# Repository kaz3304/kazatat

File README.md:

# free10u---choc

This fits within the bounds of most cheap or free sample run PCBs. 4x10 ortho with choc spacing and two bottom row options bringing you a total of 32 to 36 keys

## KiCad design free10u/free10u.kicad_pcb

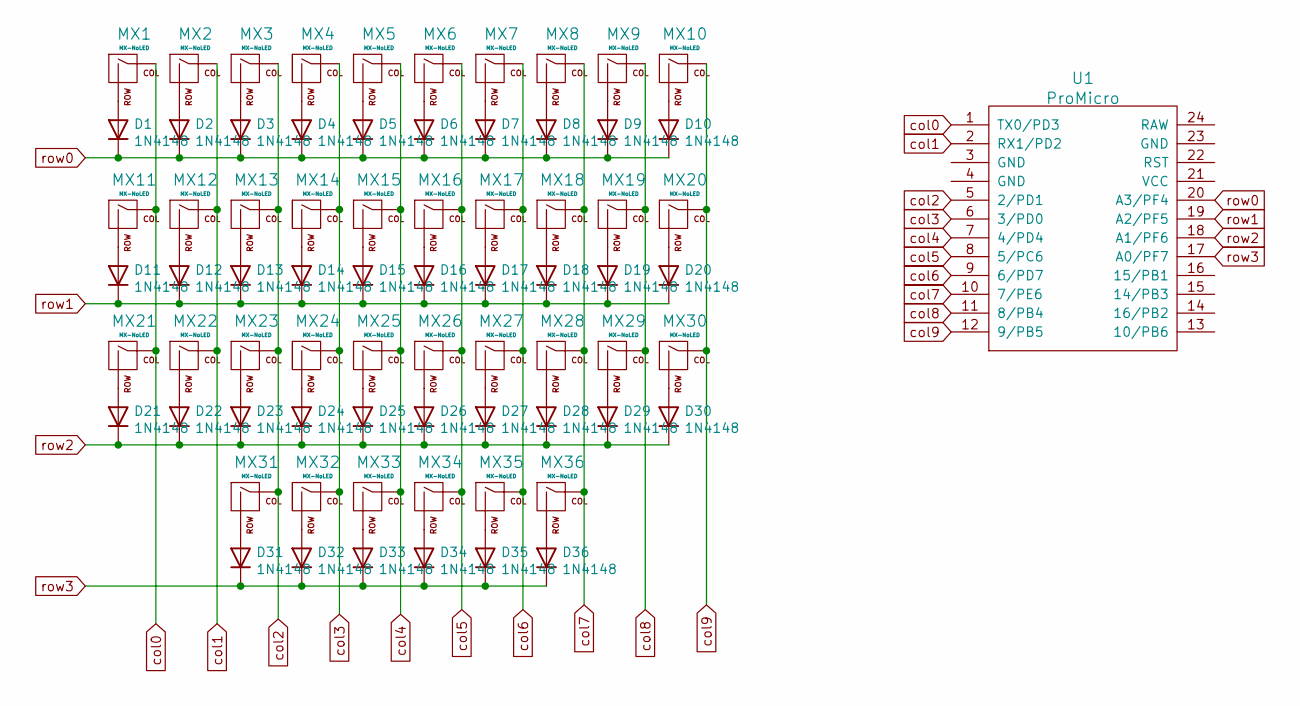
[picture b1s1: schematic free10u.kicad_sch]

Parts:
D1, D2, D3, D4, D5, D6, D7, D8, D9, D10, D11, D12, D13, D14, D15, D16, D17, D18, D19, D20, D21, D22, D23, D24, D25, D26, D27, D28, D29, D30, D31, D32, D33, D34, D35, D36: 1N4148; D_SOD-123
MX1, MX2, MX3, MX4, MX5, MX6, MX7, MX8, MX9, MX10, MX11, MX12, MX13, MX14, MX15, MX16, MX17, MX18, MX19, MX20, MX21, MX22, MX23, MX24, MX25, MX26, MX27, MX28, MX29, MX30, MX31, MX32, MX33, MX34, MX35, MX36: MX-NoLED; KailhChoc-1U
U1: ProMicro; ArduinoProMicro-TopSide

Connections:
unnamed: D1.2 (A), MX1.2 (ROW)
unnamed: D2.2 (A), MX2.2 (ROW)
unnamed: D3.2 (A), MX3.2 (ROW)
unnamed: D4.2 (A), MX4.2 (ROW)
unnamed: D5.2 (A), MX5.2 (ROW)
unnamed: D6.2 (A), MX6.2 (ROW)
unnamed: D7.2 (A), MX7.2 (ROW)
unnamed: D8.2 (A), MX8.2 (ROW)
unnamed: D9.2 (A), MX9.2 (ROW)
unnamed: D10.2 (A), MX10.2 (ROW)
unnamed: D11.2 (A), MX11.2 (ROW)
unnamed: D12.2 (A), MX12.2 (ROW)
unnamed: D13.2 (A), MX13.2 (ROW)
unnamed: D14.2 (A), MX14.2 (ROW)
unnamed: D15.2 (A), MX15.2 (ROW)
unnamed: D16.2 (A), MX16.2 (ROW)
unnamed: D17.2 (A), MX17.2 (ROW)
unnamed: D18.2 (A), MX18.2 (ROW)
unnamed: D19.2 (A), MX19.2 (ROW)
unnamed: D20.2 (A), MX20.2 (ROW)
unnamed: D21.2 (A), MX21.2 (ROW)
unnamed: D22.2 (A), MX22.2 (ROW)
unnamed: D23.2 (A), MX23.2 (ROW)
unnamed: D24.2 (A), MX24.2 (ROW)
unnamed: D25.2 (A), MX25.2 (ROW)
unnamed: D26.2 (A), MX26.2 (ROW)
unnamed: D27.2 (A), MX27.2 (ROW)
unnamed: D28.2 (A), MX28.2 (ROW)
unnamed: D29.2 (A), MX29.2 (ROW)
unnamed: D30.2 (A), MX30.2 (ROW)
unnamed: D31.2 (A), MX31.2 (ROW)
unnamed 31: D32.2 (A), MX32.2 (ROW); also elsewhere on the board
unnamed: D33.2 (A), MX33.2 (ROW)
unnamed: D34.2 (A), MX34.2 (ROW)
unnamed 34: D35.2 (A), MX35.2 (ROW); also elsewhere on the board
unnamed: D36.2 (A), MX36.2 (ROW)
col0: MX1.1 (COL), MX11.1 (COL), MX21.1 (COL), U1.1 (TX0/PD3)
col1: MX2.1 (COL), MX12.1 (COL), MX22.1 (COL), U1.2 (RX1/PD2)
col2: MX3.1 (COL), MX13.1 (COL), MX23.1 (COL), MX31.1 (COL), U1.5 (2/PD1)
col3: MX4.1 (COL), MX14.1 (COL), MX24.1 (COL), MX32.1 (COL), U1.6 (3/PD0); also elsewhere on the board
col4: MX5.1 (COL), MX15.1 (COL), MX25.1 (COL), MX33.1 (COL), U1.7 (4/PD4)
col5: MX6.1 (COL), MX16.1 (COL), MX26.1 (COL), MX34.1 (COL), U1.8 (5/PC6)
col6: MX7.1 (COL), MX17.1 (COL), MX27.1 (COL), MX35.1 (COL), U1.9 (6/PD7); also elsewhere on the board
col7: MX8.1 (COL), MX18.1 (COL), MX28.1 (COL), MX36.1 (COL), U1.10 (7/PE6)
col8: MX9.1 (COL), MX19.1 (COL), MX29.1 (COL), U1.11 (8/PB4)
col9: MX10.1 (COL), MX20.1 (COL), MX30.1 (COL), U1.12 (9/PB5)
row0: D1.1 (K), D2.1 (K), D3.1 (K), D4.1 (K), D5.1 (K), D6.1 (K), D7.1 (K), D8.1 (K), D9.1 (K), D10.1 (K), U1.20 (A3/PF4)
row1: D11.1 (K), D12.1 (K), D13.1 (K), D14.1 (K), D15.1 (K), D16.1 (K), D17.1 (K), D18.1 (K), D19.1 (K), D20.1 (K), U1.19 (A2/PF5)
row2: D21.1 (K), D22.1 (K), D23.1 (K), D24.1 (K), D25.1 (K), D26.1 (K), D27.1 (K), D28.1 (K), D29.1 (K), D30.1 (K), U1.18 (A1/PF6)
row3: D31.1 (K), D32.1 (K), D33.1 (K), D34.1 (K), D35.1 (K), D36.1 (K), U1.17 (A0/PF7)

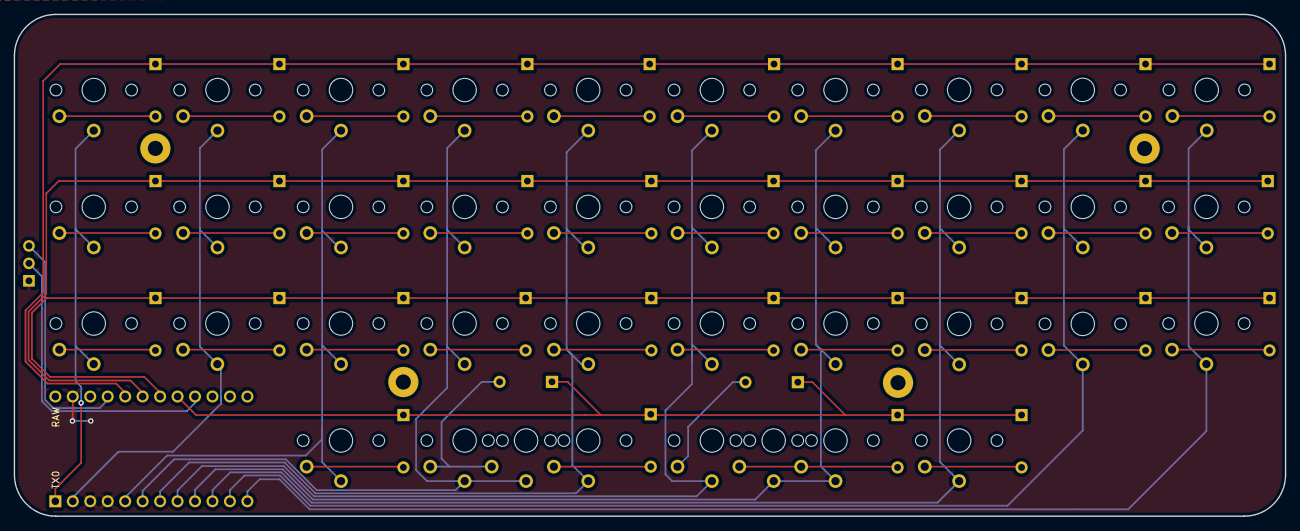
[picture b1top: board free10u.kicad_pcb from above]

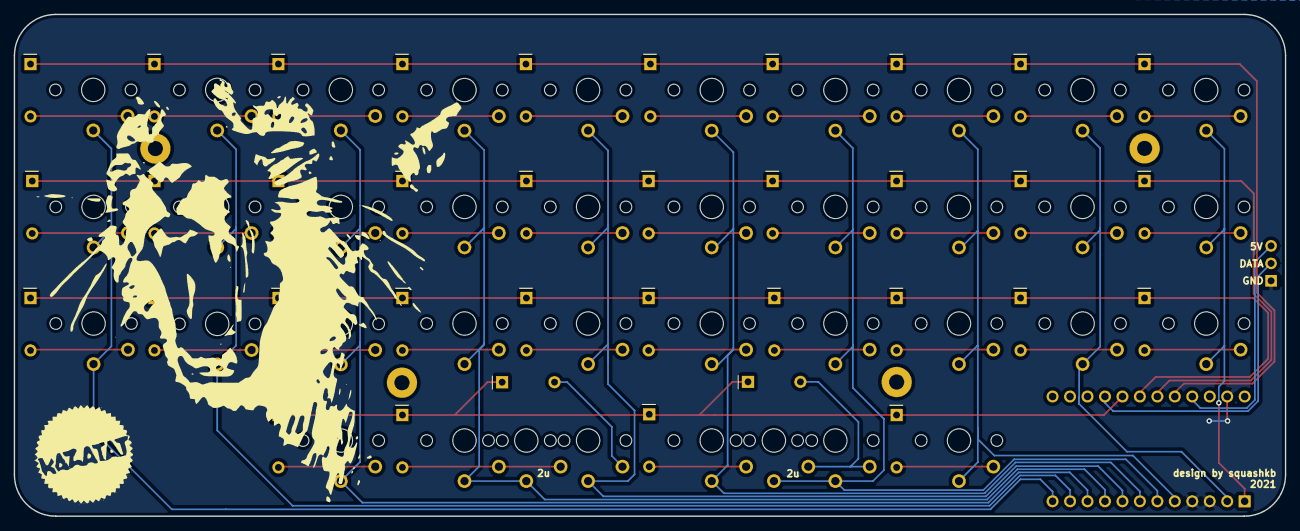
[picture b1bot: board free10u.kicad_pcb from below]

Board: 2 copper layers, 184.9 x 73.0 mm, 75 parts (36 on the bottom side), 50 nets.

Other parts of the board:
2u, 2u#2: Choc-2u-solder

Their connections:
unnamed 31: 2u#2.2; also elsewhere on the board
unnamed 34: 2u.2; also elsewhere on the board
col3: 2u#2.1; also elsewhere on the board
col6: 2u.1; also elsewhere on the board
